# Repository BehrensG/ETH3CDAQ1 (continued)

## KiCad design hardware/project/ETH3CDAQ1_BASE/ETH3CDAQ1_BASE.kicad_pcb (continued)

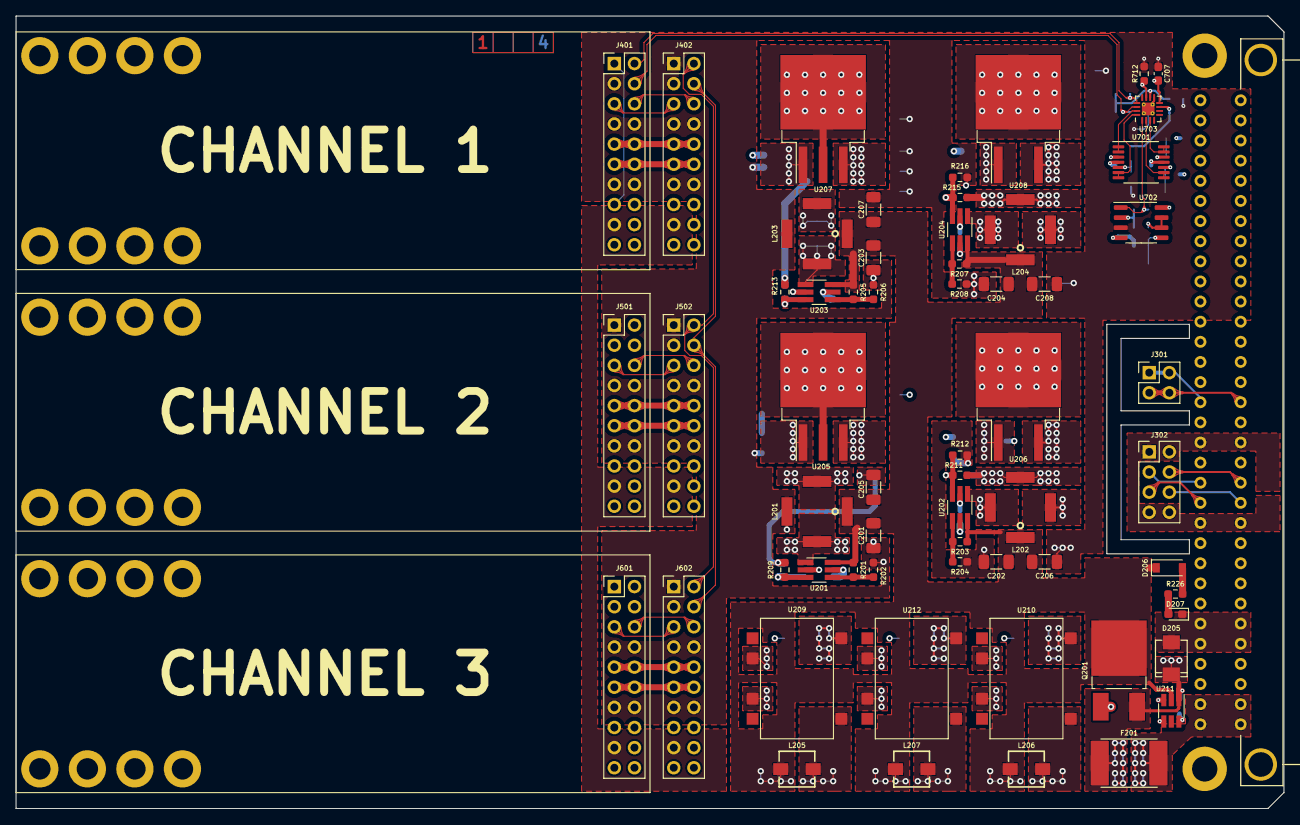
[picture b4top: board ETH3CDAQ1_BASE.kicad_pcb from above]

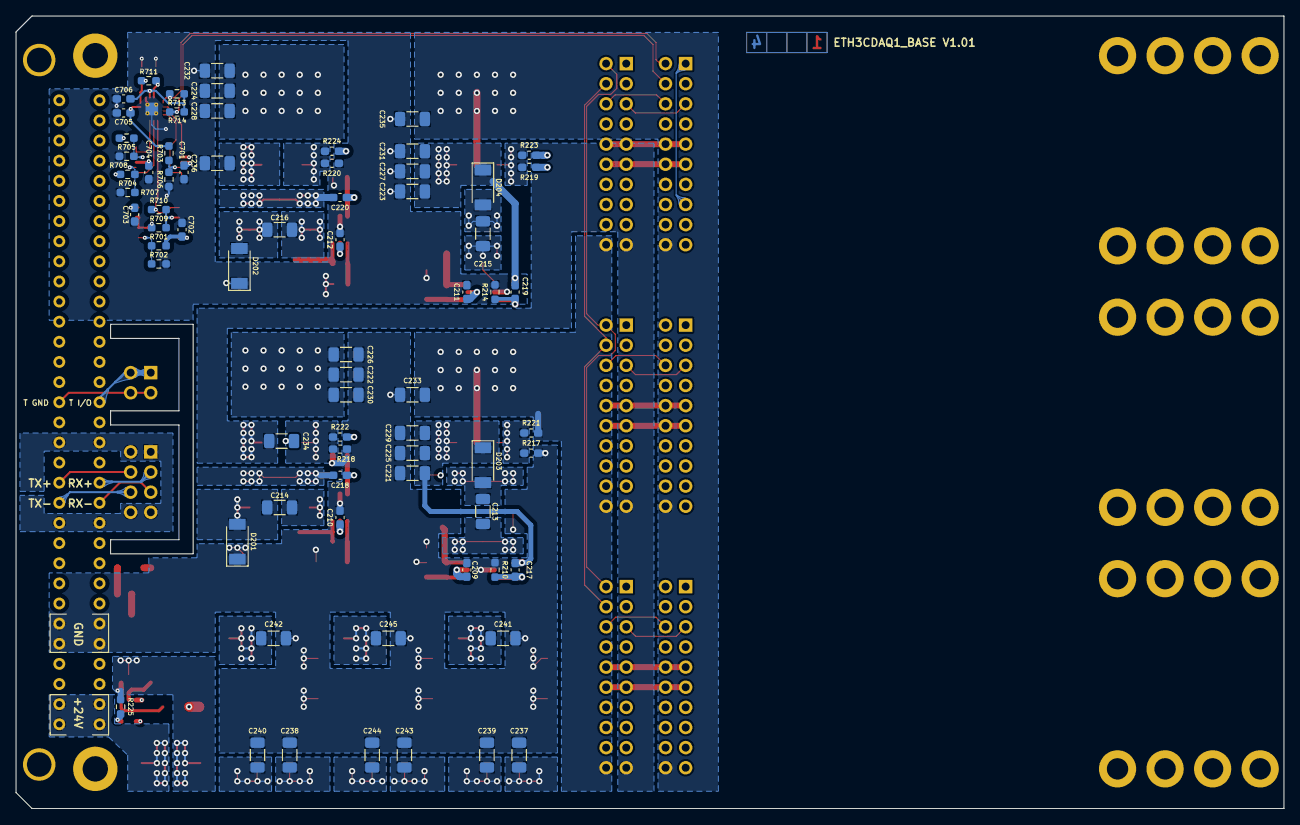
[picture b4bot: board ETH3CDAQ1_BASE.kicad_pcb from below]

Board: 4 copper layers, 160.0 x 100.0 mm, 158 parts (71 on the bottom side), 80 nets.

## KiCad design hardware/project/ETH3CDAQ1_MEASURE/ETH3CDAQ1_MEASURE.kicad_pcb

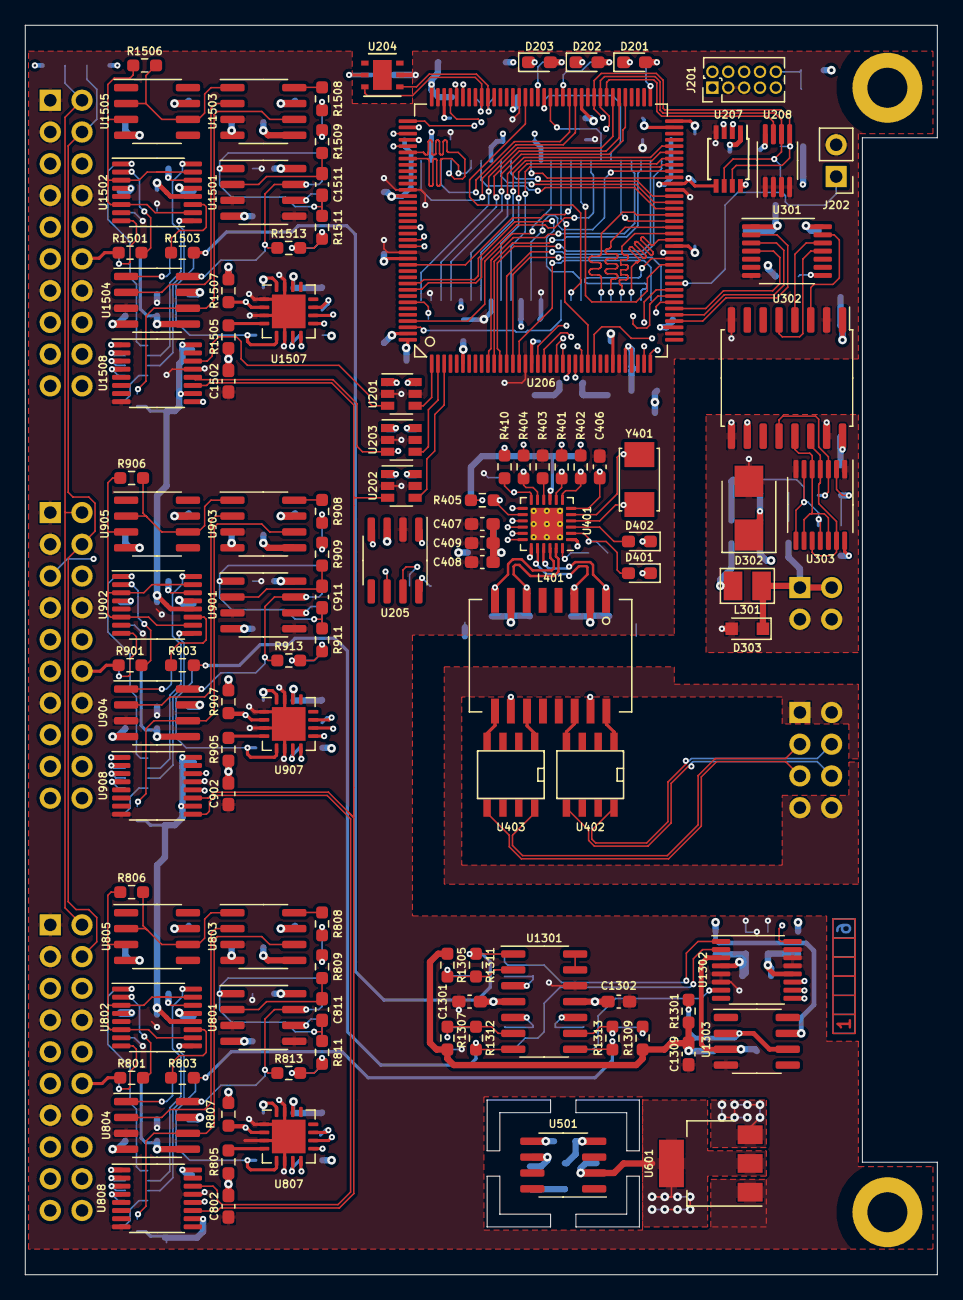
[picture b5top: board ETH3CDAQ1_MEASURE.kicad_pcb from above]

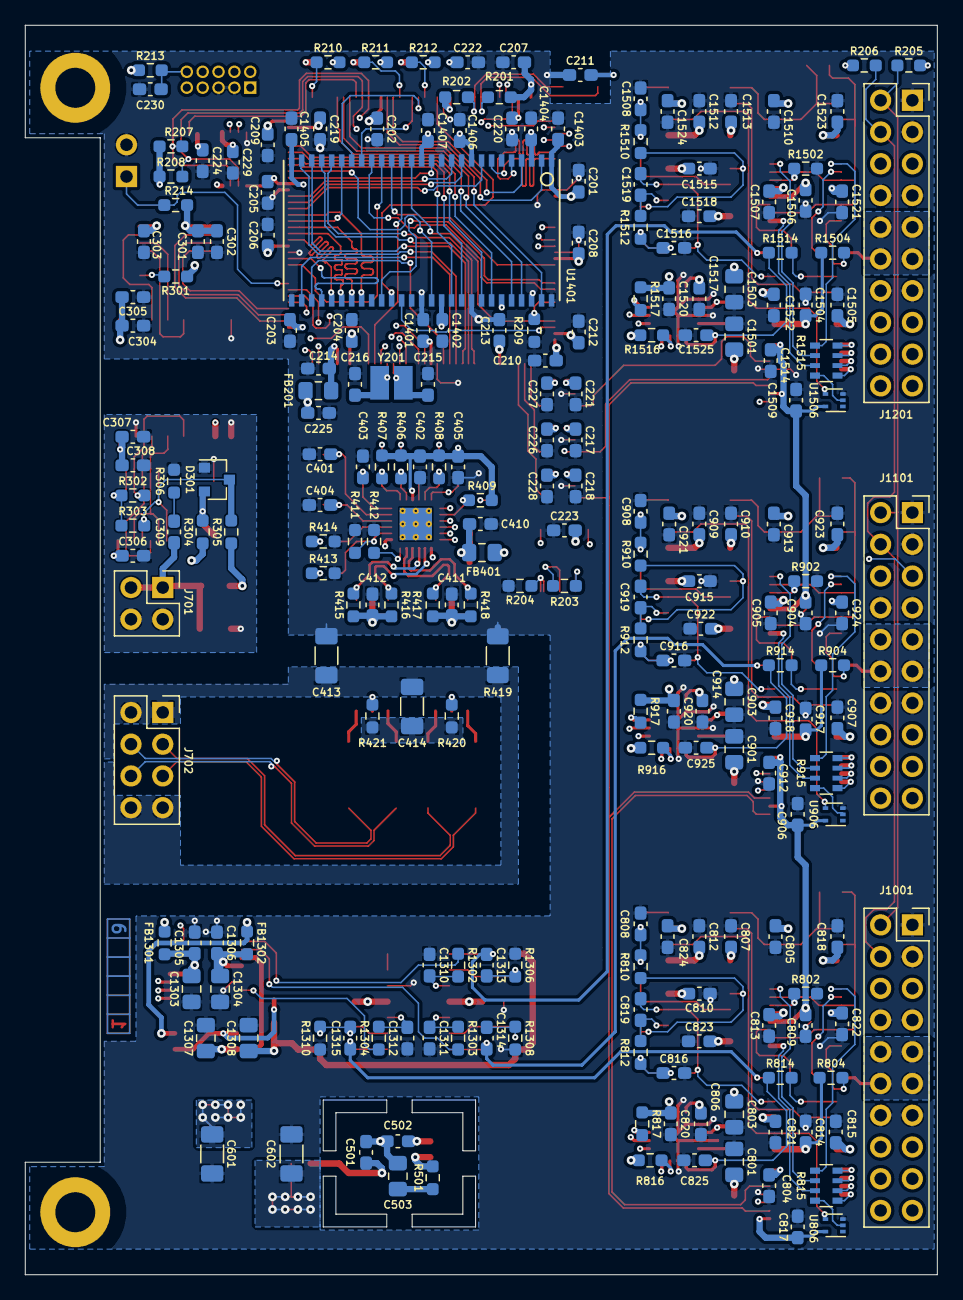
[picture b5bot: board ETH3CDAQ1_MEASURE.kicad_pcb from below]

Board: 6 copper layers, 73.0 x 100.0 mm, 330 parts (223 on the bottom side), 259 nets.

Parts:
C201, C202, C203, C204, C205, C206, C207, C208, C209, C210, C211, C212, C213, C217, C218, C221, C223, C224, C225, C226, C227, C228, C229, C230, C301, C303, C304, C306, C308, C402, C405, C408, C409, C410, C411, C412, C804, C805, C806, C807, C809, C810, C812, C813, C814, C815, C817, C818, C820, C821, C822, C823, C824, C904, C905, C906, C907, C909, C910, C912, C913, C914, C915, C917, C918, C920, C921, C922, C923, C924, C1301, C1302, C1305, C1306, C1309, C1401, C1402, C1403, C1404, C1405, C1406, C1407, C1504, C1505, C1506, C1507, C1509, C1510, C1512, C1513, C1514, C1515, C1517, C1518, C1520, C1521, C1522, C1523, C1524: 100n; C_0603_1608Metric_Pad1.08x0.95mm_HandSolder
C214, C222, C302, C305, C307, C406, C407, C501, C502, C802, C902, C1502: 1u; C_0603_1608Metric_Pad1.08x0.95mm_HandSolder
C215, C216, C401, C404: 8p; C_0603_1608Metric_Pad1.08x0.95mm_HandSolder
C219, C220: 2u2; C_0603_1608Metric_Pad1.08x0.95mm_HandSolder
C309, C819, C919, C1519: 47p; C_0603_1608Metric_Pad1.08x0.95mm_HandSolder
C403: 470p; C_0603_1608Metric_Pad1.08x0.95mm_HandSolder
C413, C414: 1n/1kV; C_1206_3216Metric_Pad1.33x1.80mm_HandSolder
C503, C803, C903, C1303, C1304, C1503: 10u; C_0805_2012Metric_Pad1.18x1.45mm_HandSolder
C601, C602: 10u; C_1206_3216Metric_Pad1.33x1.80mm_HandSolder
C801, C901, C1501: 22u; C_0805_2012Metric_Pad1.18x1.45mm_HandSolder
C808, C825, C908, C925, C1508, C1525: 330p; C_0603_1608Metric_Pad1.08x0.95mm_HandSolder
C811, C911, C1511: 100p; C_0603_1608Metric_Pad1.08x0.95mm_HandSolder
C816, C916, C1516: 1000p; C_0603_1608Metric_Pad1.08x0.95mm_HandSolder
C1307, C1308: 4u7; C_0805_2012Metric_Pad1.18x1.45mm_HandSolder
C1310, C1311, C1312: 220n; C_0603_1608Metric_Pad1.08x0.95mm_HandSolder
C1313, C1314, C1315: 1n; C_0603_1608Metric_Pad1.08x0.95mm_HandSolder
D201: RED; LED_0603_1608Metric_Pad1.05x0.95mm_HandSolder
D202, D402: GREEN; LED_0603_1608Metric_Pad1.05x0.95mm_HandSolder
D203: BLUE; LED_0603_1608Metric_Pad1.05x0.95mm_HandSolder
D301: BAV99; SOT-23
D302: SMBJ5.0A; D_SMB
D303: SD36C-01FTG; D_SOD-323_HandSoldering
D401: YELLOW; LED_0603_1608Metric_Pad1.05x0.95mm_HandSolder
FB201, FB401: 742792031; L_0805_2012Metric_Pad1.15x1.40mm_HandSolder
FB1301, FB1302: MPZ1608S221ATA00; R_0603_1608Metric_Pad0.98x0.95mm_HandSolder
H101, H102: MountingHole; MountingHole_3.2mm_M3_DIN965_Pad
J201: 20021111-00010T4LF; PinHeader_2x05_P1.27mm_Vertical
J202: Conn_02x01; PinHeader_1x02_P2.54mm_Vertical
J701: Conn_02x02_Odd_Even; PinSocket_2x02_P2.54mm_Vertical
J702: Conn_02x04_Odd_Even; PinSocket_2x04_P2.54mm_Vertical
J1001, J1101, J1201: Conn_02x10_Odd_Even; PinSocket_2x10_P2.54mm_Vertical
L301: CW252016-R33G; CW252016
L401: 749010012A
R201, R202, R205, R206, R207, R208: 4k7; R_0603_1608Metric_Pad0.98x0.95mm_HandSolder
R203: 120; R_0603_1608Metric_Pad0.98x0.95mm_HandSolder
R204: R; R_0603_1608Metric_Pad0.98x0.95mm_HandSolder
R209, R213, R214, R301, R403, R406, R407, R408, R409, R411, R802, R803, R816, R817, R902, R903, R916, R917, R1502, R1503, R1516, R1517: 10k; R_0603_1608Metric_Pad0.98x0.95mm_HandSolder
R210, R212: 680; R_0603_1608Metric_Pad0.98x0.95mm_HandSolder
R211: 560; R_0603_1608Metric_Pad0.98x0.95mm_HandSolder
R302: 14k7; R_0603_1608Metric_Pad0.98x0.95mm_HandSolder
R303: 100; R_0603_1608Metric_Pad0.98x0.95mm_HandSolder
R304, R1302, R1303, R1304: 1k; R_0603_1608Metric_Pad0.98x0.95mm_HandSolder
R305: 47; R_0603_1608Metric_Pad0.98x0.95mm_HandSolder
R306: 51R1; R_0603_1608Metric_Pad0.98x0.95mm_HandSolder
R401, R402, R404, R405: 33; R_0603_1608Metric_Pad0.98x0.95mm_HandSolder
R410: 1k5; R_0603_1608Metric_Pad0.98x0.95mm_HandSolder
R412: 12k1; R_0603_1608Metric_Pad0.98x0.95mm_HandSolder
R413, R414: 270; R_0603_1608Metric_Pad0.98x0.95mm_HandSolder
R415, R416, R417, R418, R804, R904, R1504: 49R9; R_0603_1608Metric_Pad0.98x0.95mm_HandSolder
R419: 1M/1kV; R_1206_3216Metric_Pad1.30x1.75mm_HandSolder
R420, R421: 75/1%; R_0603_1608Metric_Pad0.98x0.95mm_HandSolder
R501, R805, R905, R1505: 0R22; R_0603_1608Metric_Pad0.98x0.95mm_HandSolder
R801, R806, R814, R901, R906, R914, R1501, R1506, R1514: 0; R_0603_1608Metric_Pad0.98x0.95mm_HandSolder
R807, R907, R1507: 0R47; R_0603_1608Metric_Pad0.98x0.95mm_HandSolder
R808, R810, R908, R910, R1508, R1510: 6k81; R_0603_1608Metric_Pad0.98x0.95mm_HandSolder
R809, R909, R1509: 11k3; R_0603_1608Metric_Pad0.98x0.95mm_HandSolder
R811, R813, R911, R913, R1511, R1513: 5k23; R_0603_1608Metric_Pad0.98x0.95mm_HandSolder
R812, R912, R1512: 10k2; R_0603_1608Metric_Pad0.98x0.95mm_HandSolder
R815, R915, R1515: 680; R_Array_Convex_4x0603
R1301: 10; R_0603_1608Metric_Pad0.98x0.95mm_HandSolder
R1305, R1307, R1309: 24k9; R_0603_1608Metric_Pad0.98x0.95mm_HandSolder
R1306, R1308, R1310: 33k2; R_0603_1608Metric_Pad0.98x0.95mm_HandSolder
R1311, R1312, R1313: 100k; R_0603_1608Metric_Pad0.98x0.95mm_HandSolder
U201, U202, U203: SN74LVC1T45DBV; SOT-23-6
U204: HDC1080; Texas_PWSON-N6
U205: MCP2551-I-SN; SOIC-8_3.9x4.9mm_P1.27mm
U206: STM32H743ZI; TQFP-144_20x20mm_P0.5mm
U207: PCA9517; TSSOP-8_3x3mm_P0.65mm
U208: 24LC08B-E/MS; MSOP-8_3x3mm_P0.65mm
U301: TXB0104PW; TSSOP-14_4.4x5mm_P0.65mm
U302: ADuM5402; SOIC-16W_7.5x10.3mm_P1.27mm
U303: 74AC125; TSSOP-14_4.4x5mm_P0.65mm
U401: LAN8742A; QFN-24-1EP_4x4mm_P0.5mm_EP2.6x2.6mm_ThermalVias
U402, U403: LC03-3.3; SO8E
U501: REF5040ID; SOIC-8_3.9x4.9mm_P1.27mm
U601: LM1117-5.0; SOT-223-3_TabPin2
U801, U901, U1501: LT1355; SOIC-8_3.9x4.9mm_P1.27mm
U802, U902, U1502: DG211; TSSOP-16_4.4x5mm_P0.65mm
U803, U804, U903, U904, U1503, U1504: DG419LDY; SOIC-8_3.9x4.9mm_P1.27mm
U805, U905, U1505: OPA192; SOIC-8_3.9x4.9mm_P1.27mm
U806, U906, U1506: 74LVC1GU04DRL; SOT-553
U807, U907, U1507: ADS8681RUM; QFN-16-1EP_4x4mm_P0.65mm_EP2.7x2.7mm
U808, U908, U1508: 74HCT595; TSSOP-16_4.4x5mm_P0.65mm
U1301: TL074; SOIC-14_3.9x8.7mm_P1.27mm
U1302: DAC8564; TSSOP-16_4.4x5mm_P0.65mm
U1303: TL071; SOIC-8_3.9x4.9mm_P1.27mm
U1401: IS42S16400J-xC/MT48LC16M16A2P-6A; TSSOP-54
Y201: NX3225GD-8MHZ; NX3225GD
Y401: NX5032GA-25.000M-LN-CD-1; NX5032GA

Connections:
+3V3: C201.1, C202.1, C203.1, C204.1, C205.1, C206.1, C207.1, C208.1, C209.1, C210.1, C211.1, C212.1, C213.1, C222.1, C224.1, C225.1, C226.1, C227.1, C228.1, C229.1, C301.1, C302.1, C402.1, C405.1, C820.1, C920.1, C1401.1, C1402.1, C1403.1, C1404.1, C1405.1, C1406.1, C1407.1, C1520.1, D201.2, D202.2, D203.2, FB201.2, FB401.2, FB1301.2, J201.1, J1001.15, J1001.16, J1101.15, J1101.16, J1201.15, J1201.16, R201.1, R202.1, R205.1, R206.1, R207.1, R208.1, R213.1, R214.2, R301.1, R406.1, R407.1, R408.1, R409.1, R410.1, R816.1, R817.1, R916.1, R917.1, R1516.1, R1517.1, U201.6, U202.6, U203.6, U204.5, U206.6, U206.17, U206.30, U206.39, U206.52, U206.62, U206.72, U206.84, U206.95, U206.108, U206.121, U206.131, U206.143, U206.144, U207.1, U207.5, U207.8, U208.8, U301.1, U401.9, U807.14, U907.14, U1401.1, U1401.3, U1401.9, U1401.14, U1401.27, U1401.43, U1401.49, U1507.14
+5V: C217.1, C218.1, C221.1, C223.1, C303.1, C304.1, C305.1, C804.1, C806.1, C809.1, C812.1, C814.1, C817.1, C904.1, C906.1, C909.1, C912.1, C914.1, C917.1, C1504.1, C1506.1, C1509.1, C1512.1, C1514.1, C1517.1, J1001.18, J1101.18, J1201.18, R804.2, R904.2, R1504.2, U201.1, U202.1, U203.1, U205.3, U301.14, U302.1, U802.12, U803.5, U804.5, U806.5, U807.16, U808.10, U808.16, U902.12, U903.5, U904.5, U906.5, U907.16, U908.10, U908.16, U1502.12, U1503.5, U1504.5, U1506.5, U1507.16, U1508.10, U1508.16
+5VF: C501.1, C602.1, FB1302.2, U501.2, U601.2, U1303.7
+5V_TRIG: C306.1, C307.1, C308.1, R304.1, U302.10, U302.16, U303.14
+9V: C601.1, J1001.17, J1101.17, J1201.17, U601.3
+18V: C805.1, C807.1, C810.1, C813.1, C815.1, C905.1, C907.1, C910.1, C913.1, C915.1, C1301.1, C1505.1, C1507.1, C1510.1, C1513.1, C1515.1, J1001.20, J1101.20, J1201.20, U801.8, U802.13, U803.4, U804.4, U805.7, U901.8, U902.13, U903.4, U904.4, U905.7, U1301.4, U1501.8, U1502.13, U1503.4, U1504.4, U1505.7
-18V: C818.1, C821.1, C822.1, C823.1, C824.1, C918.1, C921.1, C922.1, C923.1, C924.1, C1302.1, C1518.1, C1521.1, C1522.1, C1523.1, C1524.1, J1001.19, J1101.19, J1201.19, U801.4, U802.4, U803.7, U804.7, U805.4, U901.4, U902.4, U903.7, U904.7, U905.4, U1301.11, U1501.4, U1502.4, U1503.7, U1504.7, U1505.4
/CH1 Connector/CANH: J1001.5, J1101.5, J1201.5, R203.1, U205.7
/CH1 Connector/CANL: J1001.6, J1101.6, J1201.6, R203.2, U205.6
/CH1 Connector/CH1_IN: J1201.9, J1201.10, J1201.11, J1201.12, R1501.2
/CH1 Connector/I2C_SCL: J1001.2, J1101.2, J1201.2, R205.2, U207.2
/CH1 Connector/I2C_SDA: J1001.4, J1101.4, J1201.4, R206.2, U207.3
/CH2 Connector/CH2_IN: J1101.9, J1101.10, J1101.11, J1101.12, R901.2
/CH3 Connector/CH3_IN: J1001.9, J1001.10, J1001.11, J1001.12, R801.2
/Channel 1/ADC1_SCLK: U206.111, U807.10, U907.10, U1507.10
/Channel 1/ADC1_SDI: U206.113, U1507.8
/Channel 1/ADC1_SDO: R1517.2, U907.8, U1507.11
/Channel 1/ADC1_~CS: U206.110, U807.9, U907.9, U1507.9
/Channel 1/CH1_LPF: R1515.4, U1506.2
/Channel 1/CH1_M_DAC: R1515.3, U1502.9
/Channel 1/CH1_M_GND: R1515.2, U1502.16
/Channel 1/CH1_M_IN: R1515.1, U1502.1
/Channel 1/DAC_V1: C1313.1, R1311.1, R1503.2, U1301.1
/Channel 1/REFCAP1: R1505.2, U1507.4
/Channel 1/SR1_QH: U908.14, U1508.9
/Channel 2/ADC2_SDO: R917.2, U807.8, U907.11
/Channel 2/CH2_LPF: R915.4, U906.2
/Channel 2/CH2_M_DAC: R915.3, U902.9
/Channel 2/CH2_M_GND: R915.2, U902.16
/Channel 2/CH2_M_IN: R915.1, U902.1
/Channel 2/DAC_V2: C1314.1, R903.2, R1312.1, U1301.7
/Channel 2/REFCAP2: R905.2, U907.4
/Channel 2/SR2_QH: U808.14, U908.9
/Channel 3/ADC3_SDO: R817.2, U206.112, U807.11
/Channel 3/CH3_LPF: R815.4, U806.2
/Channel 3/CH3_M_DAC: R815.3, U802.9
/Channel 3/CH3_M_GND: R815.2, U802.16
/Channel 3/CH3_M_IN: R815.1, U802.1
/Channel 3/DAC_V3: C1315.1, R803.2, R1313.1, U1301.8
/Channel 3/REFCAP3: R805.2, U807.4
/Connector 1/EXT_TRIG: C309.1, D303.1, J701.1, J701.2, L301.1
/Connector 1/RX+: J702.3, U403.8
/Connector 1/RX-: J702.5, U403.5
/Connector 1/TX+: J702.4, U402.8
/Connector 1/TX-: J702.6, U402.5
/DAC/+2V5REF: C1308.1, C1309.1, R1301.1, R1305.2, R1307.2, R1309.2
/DAC/DAC_0-2V5_VOUT1: R1302.2, U1302.1
/DAC/DAC_0-2V5_VOUT2: R1303.2, U1302.2
/DAC/DAC_0-2V5_VOUT3: R1304.2, U1302.7
/DAC/DAC_DIN: U206.21, U1302.11
/DAC/DAC_LDAC: U206.22, U1302.16
/DAC/DAC_SCLK: U206.19, U1302.10
/DAC/DAC_~SYNC: U206.18, U1302.9
/Ethernet/ETH_RXN: L401.8, R418.2, U401.22
/Ethernet/ETH_RXP: L401.6, R417.2, U401.23
/Ethernet/ETH_TXN: L401.3, R416.2, U401.20
/Ethernet/ETH_TXP: L401.1, R415.2, U401.21
/Ethernet/MODE0: R401.1, R406.2, U401.8
/Ethernet/MODE1: R402.1, R407.2, U401.7
/Ethernet/MODE2: R404.1, R408.2, U401.11
/Ethernet/NRST: C230.1, J201.10, R213.2, U206.25, U401.15
/Ethernet/REFCLK0: R405.1, R409.2, U401.14
/Ethernet/REF_CLK: R405.2, U206.35
/Ethernet/RMII_CRS_DV: R404.2, U206.43
/Ethernet/RMII_MDC: U206.27, U401.13
/Ethernet/RMII_MDIO: R410.2, U206.36, U401.12
/Ethernet/RMII_RXD0: R401.2, U206.44
/Ethernet/RMII_RXD1: R402.2, U206.45
/Ethernet/RMII_TXD0: U206.128, U401.17
/Ethernet/RMII_TXD1: U206.129, U401.18
/Ethernet/RMII_TXEN: U206.126, U401.16
/MCU/A0: U206.10, U1401.23
/MCU/A1: U206.11, U1401.24
/MCU/A2: U206.12, U1401.25
/MCU/A3: U206.13, U1401.26
/MCU/A4: U206.14, U1401.29
/MCU/A5: U206.15, U1401.30
/MCU/A6: U206.50, U1401.31
/MCU/A7: U206.53, U1401.32
/MCU/A8: U206.54, U1401.33
/MCU/A9: U206.55, U1401.34
/MCU/A10: U206.56, U1401.22
/MCU/A11: U206.57, U1401.35
/MCU/BA0: U206.89, U1401.20
/MCU/BA1: U206.90, U1401.21
/MCU/CAN_RX: U205.4, U206.103
/MCU/CAN_TX: U205.1, U206.104
/MCU/CKE: U206.135, U1401.37
/MCU/CLK: U206.93, U1401.38
/MCU/D0: U206.85, U1401.2
/MCU/D1: U206.86, U1401.4
/MCU/D2: U206.114, U1401.5
/MCU/D3: U206.115, U1401.7
/MCU/D4: U206.58, U1401.8
/MCU/D5: U206.59, U1401.10
/MCU/D6: U206.60, U1401.11
/MCU/D7: U206.63, U1401.13
/MCU/D8: U206.64, U1401.42
/MCU/D9: U206.65, U1401.44
/MCU/D10: U206.66, U1401.45
/MCU/D11: U206.67, U1401.47
/MCU/D12: U206.68, U1401.48
/MCU/D13: U206.77, U1401.50
/MCU/D14: U206.78, U1401.51
/MCU/D15: U206.79, U1401.53
/MCU/EEPROM_SCL: R208.2, U206.81, U207.6, U208.6
/MCU/EEPROM_SDA: R207.2, U206.82, U207.7, U208.5
/MCU/EEPROM_WP: U206.80, U208.7
/MCU/LDQM: U206.141, U1401.15
/MCU/MCU_SR_CLK: U202.4, U206.3
/MCU/MCU_SR_DAT: U201.4, U206.1
/MCU/MCU_SR_LAT: U203.4, U206.2
/MCU/MCU_VDDA: C214.1, FB201.1, U206.32, U206.33
/MCU/SD_CLK: U202.3, U808.11, U908.11, U1508.11
/MCU/SD_DAT: U201.3, U1508.14
/MCU/SD_LAT: U203.3, U808.12, U908.12, U1508.12
/MCU/SENS_SCL: R201.2, U204.6, U206.100
/MCU/SENS_SDA: R202.2, U204.1, U206.99
/MCU/TCK_SWCLK: J201.4, U206.109
/MCU/TMS_SWDIO: J201.2, U206.105
/MCU/TRIG_EN: U206.40, U301.2
/MCU/TRIG_IN: U206.42, U301.4
/MCU/TRIG_OUT: U206.41, U301.3
/MCU/UDQM: U206.142, U1401.39
/MCU/~CAS: U206.132, U1401.17
/MCU/~CS: U206.136, U1401.19
/MCU/~RAS: U206.49, U1401.18
/MCU/~WE: U206.26, U1401.16
/Trigger/EXT_TRIG_SIGN: R302.1, U302.12, U303.3
/Trigger/TRIG_OUT_EN: U302.14, U303.4, U303.10, U303.13
/Trigger/TRIG_OUT_SIGN: U302.13, U303.5, U303.9, U303.12
Earth: C413.1, C414.2, J702.1, J702.2, J702.7, J702.8, R419.1
GND: C201.2, C202.2, C203.2, C204.2, C205.2, C206.2, C207.2, C208.2, C209.2, C210.2, C211.2, C212.2, C213.2, C214.2, C215.2, C216.2, C217.2, C218.2, C219.2, C220.2, C221.2, C222.2, C223.2, C224.2, C225.2, C226.2, C227.2, C228.2, C229.2, C230.2, C301.2, C302.2, C303.2, C304.2, C305.2, C401.2, C402.2, C403.2, C404.2, C405.2, C406.2, C407.2, C408.2, C409.2, C410.2, C411.2, C412.2, C413.2, C501.2, C502.2, C503.2, C601.2, C602.2, C801.2, C802.2, C803.2, C804.2, C805.2, C806.2, C807.2, C808.2, C809.2, C810.2, C812.2, C813.2, C814.2, C815.2, C816.2, C817.2, C818.2, C820.2, C821.2, C822.2, C823.2, C824.2, C825.2, C901.2, C902.2, C903.2, C904.2, C905.2, C906.2, C907.2, C908.2, C909.2, C910.2, C912.2, C913.2, C914.2, C915.2, C916.2, C917.2, C918.2, C920.2, C921.2, C922.2, C923.2, C924.2, C925.2, C1301.2, C1302.2, C1303.2, C1304.2, C1305.2, C1306.2, C1307.2, C1308.2, C1309.2, C1310.2, C1311.2, C1312.2, C1401.2, C1402.2, C1403.2, C1404.2, C1405.2, C1406.2, C1407.2, C1501.2, C1502.2, C1503.2, C1504.2, C1505.2, C1506.2, C1507.2, C1508.2, C1509.2, C1510.2, C1512.2, C1513.2, C1514.2, C1515.2, C1516.2, C1517.2, C1518.2, C1520.2, C1521.2, C1522.2, C1523.2, C1524.2, C1525.2, J201.3, J201.5, J202.2, J1001.1, J1001.3, J1001.7, J1001.8, J1001.13, J1001.14, J1101.1, J1101.3, J1101.7, J1101.8, J1101.13, J1101.14, J1201.1, J1201.3, J1201.7, J1201.8, J1201.13, J1201.14, R204.2, R209.2, R403.2, R411.2, R412.1, R413.2, R414.2, R419.2, R802.2, R902.2, R1306.2, R1308.2, R1310.2, R1502.2, U201.2, U201.5, U202.2, U202.5, U203.2, U203.5, U204.2, U205.2, U206.16, U206.31, U206.38, U206.51, U206.61, U206.83, U206.94, U206.107, U206.120, U206.130, U207.4, U208.1, U208.2, U208.3, U208.4, U301.7, U302.2, U302.8, U401.25, U501.4, U601.1, U801.3, U801.5, U802.5, U803.3, U804.3, U806.3, U807.1, U807.3, U807.6, U807.15, U807.17, U808.8, U808.13, U901.3, U901.5, U902.5, U903.3, U904.3, U906.3, U907.1, U907.3, U907.6, U907.15, U907.17, U908.8, U908.13, U1301.12, U1302.5, U1302.6, U1302.13, U1302.14, U1302.15, U1303.4, U1401.6, U1401.12, U1401.28, U1401.41, U1401.46, U1401.52, U1401.54, U1501.3, U1501.5, U1502.5, U1503.3, U1504.3, U1506.3, U1507.1, U1507.3, U1507.6, U1507.15, U1507.17, U1508.8, U1508.13
GND_TRIG: C306.2, C307.2, C308.2, D301.1, D302.2, D303.2, J701.3, J701.4, R306.2, U302.9, U302.15, U303.1, U303.7
unnamed: C215.1, U206.23, Y201.1
unnamed: C216.1, U206.24, Y201.2
unnamed: C219.1, U206.71
unnamed: C220.1, U206.106
unnamed: C309.2, R306.1
unnamed: C401.1, U401.5, Y401.2
unnamed: C403.1, C406.1, U401.6
unnamed: C404.1, U401.4, Y401.1
unnamed: C414.1, R420.2, R421.2
unnamed: C502.1, U501.5
unnamed: C503.1, R501.2
unnamed: C801.1, C802.1, R805.1
unnamed: C803.1, R807.2
unnamed: C808.1, R808.1, R809.2, R810.2
unnamed: C811.1, R810.1, R811.2, U801.1
unnamed: C811.2, R809.1, U801.2
unnamed: C816.1, R811.1, R812.2, R813.2
unnamed: C819.1, R813.1, U801.7, U804.8
unnamed: C819.2, R812.1, U801.6
unnamed: C825.1, R814.1, U807.5
unnamed: C901.1, C902.1, R905.1
unnamed: C903.1, R907.2
unnamed: C908.1, R908.1, R909.2, R910.2
unnamed: C911.1, R910.1, R911.2, U901.1
unnamed: C911.2, R909.1, U901.2
unnamed: C916.1, R911.1, R912.2, R913.2
unnamed: C919.1, R913.1, U901.7, U904.8
unnamed: C919.2, R912.1, U901.6
unnamed: C925.1, R914.1, U907.5
unnamed: C1303.1, C1305.1, FB1301.1, U1302.12
unnamed: C1304.1, C1306.1, FB1302.1, U1302.4
unnamed: C1307.1, U1302.3, U1303.3
unnamed: C1310.1, R1302.1, U1301.3
unnamed: C1311.1, R1303.1, U1301.5
unnamed: C1312.1, R1304.1, U1301.10
unnamed: C1313.2, R1305.1, R1306.1, R1311.2, U1301.2
unnamed: C1314.2, R1307.1, R1308.1, R1312.2, U1301.6
unnamed: C1315.2, R1309.1, R1310.1, R1313.2, U1301.9
unnamed: C1501.1, C1502.1, R1505.1
unnamed: C1503.1, R1507.2
unnamed: C1508.1, R1508.1, R1509.2, R1510.2
unnamed: C1511.1, R1510.1, R1511.2, U1501.1
unnamed: C1511.2, R1509.1, U1501.2
unnamed: C1516.1, R1511.1, R1512.2, R1513.2
unnamed: C1519.1, R1513.1, U1501.7, U1504.8
unnamed: C1519.2, R1512.1, U1501.6
unnamed: C1525.1, R1514.1, U1507.5
unnamed: D201.1, R210.2
unnamed: D202.1, R211.2
unnamed: D203.1, R212.2
unnamed: D301.2, D302.1, R304.2
unnamed: D301.3, R303.2, R305.1, U303.6, U303.8, U303.11
unnamed: D401.1, R413.1
unnamed: D401.2, R411.1, U401.2
unnamed: D402.1, R414.1
unnamed: D402.2, U401.3
unnamed: J202.1, R214.1, U206.46
unnamed: L301.2, R305.2
unnamed: L401.9, U403.4
unnamed: L401.10, R420.1
unnamed: L401.11, U403.1
unnamed: L401.14, U402.4
unnamed: L401.15, R421.1
unnamed: L401.16, U402.1
unnamed: R204.1, U205.8
unnamed: R209.1, U206.138
unnamed: R210.1, U206.73
unnamed: R211.1, U206.87
unnamed: R212.1, U206.91
unnamed: R301.2, U301.8
unnamed: R302.2, R303.1, U303.2
unnamed: R403.1, U401.10
unnamed: R412.2, U401.24
unnamed: R801.1, U802.2
unnamed: R802.1, U802.14
unnamed: R803.1, U802.11
unnamed: R804.1, U802.8
unnamed: R806.1, U803.1, U805.2, U805.6
unnamed: R806.2, U802.3, U802.6, U802.10, U802.15, U805.3
unnamed: R808.2, U803.8
unnamed: R814.2, U804.1
unnamed: R815.5, U808.4
unnamed: R815.6, U808.3
unnamed: R815.7, U808.2
unnamed: R815.8, U808.1
unnamed: R816.2, U807.7
unnamed: R901.1, U902.2
unnamed: R902.1, U902.14
unnamed: R903.1, U902.11
unnamed: R904.1, U902.8
unnamed: R906.1, U903.1, U905.2, U905.6
unnamed: R906.2, U902.3, U902.6, U902.10, U902.15, U905.3
unnamed: R908.2, U903.8
unnamed: R914.2, U904.1
unnamed: R915.5, U908.4
unnamed: R915.6, U908.3
unnamed: R915.7, U908.2
unnamed: R915.8, U908.1
unnamed: R916.2, U907.7
unnamed: R1301.2, U1303.2, U1303.6
unnamed: R1501.1, U1502.2
unnamed: R1502.1, U1502.14
unnamed: R1503.1, U1502.11
unnamed: R1504.1, U1502.8
unnamed: R1506.1, U1503.1, U1505.2, U1505.6
unnamed: R1506.2, U1502.3, U1502.6, U1502.10, U1502.15, U1505.3
unnamed: R1508.2, U1503.8
unnamed: R1514.2, U1504.1
unnamed: R1515.5, U1508.4
unnamed: R1515.6, U1508.3
unnamed: R1515.7, U1508.2
unnamed: R1515.8, U1508.1
unnamed: R1516.2, U1507.7
unnamed: U301.11, U302.5
unnamed: U301.12, U302.4
unnamed: U301.13, U302.3
unnamed: U803.2, U804.2
unnamed: U803.6, U804.6, U806.4
unnamed: U903.2, U904.2
unnamed: U903.6, U904.6, U906.4
unnamed: U1301.13, U1301.14
unnamed: U1503.2, U1504.2
unnamed: U1503.6, U1504.6, U1506.4
VCCQ: C407.1, C408.1, C409.1, C410.1, C411.1, C412.1, FB401.1, L401.2, L401.7, R415.1, R416.1, R417.1, R418.1, U401.1, U401.19
VREF: R501.1, R807.1, R907.1, R1507.1, U501.6, U807.2, U907.2, U1507.2

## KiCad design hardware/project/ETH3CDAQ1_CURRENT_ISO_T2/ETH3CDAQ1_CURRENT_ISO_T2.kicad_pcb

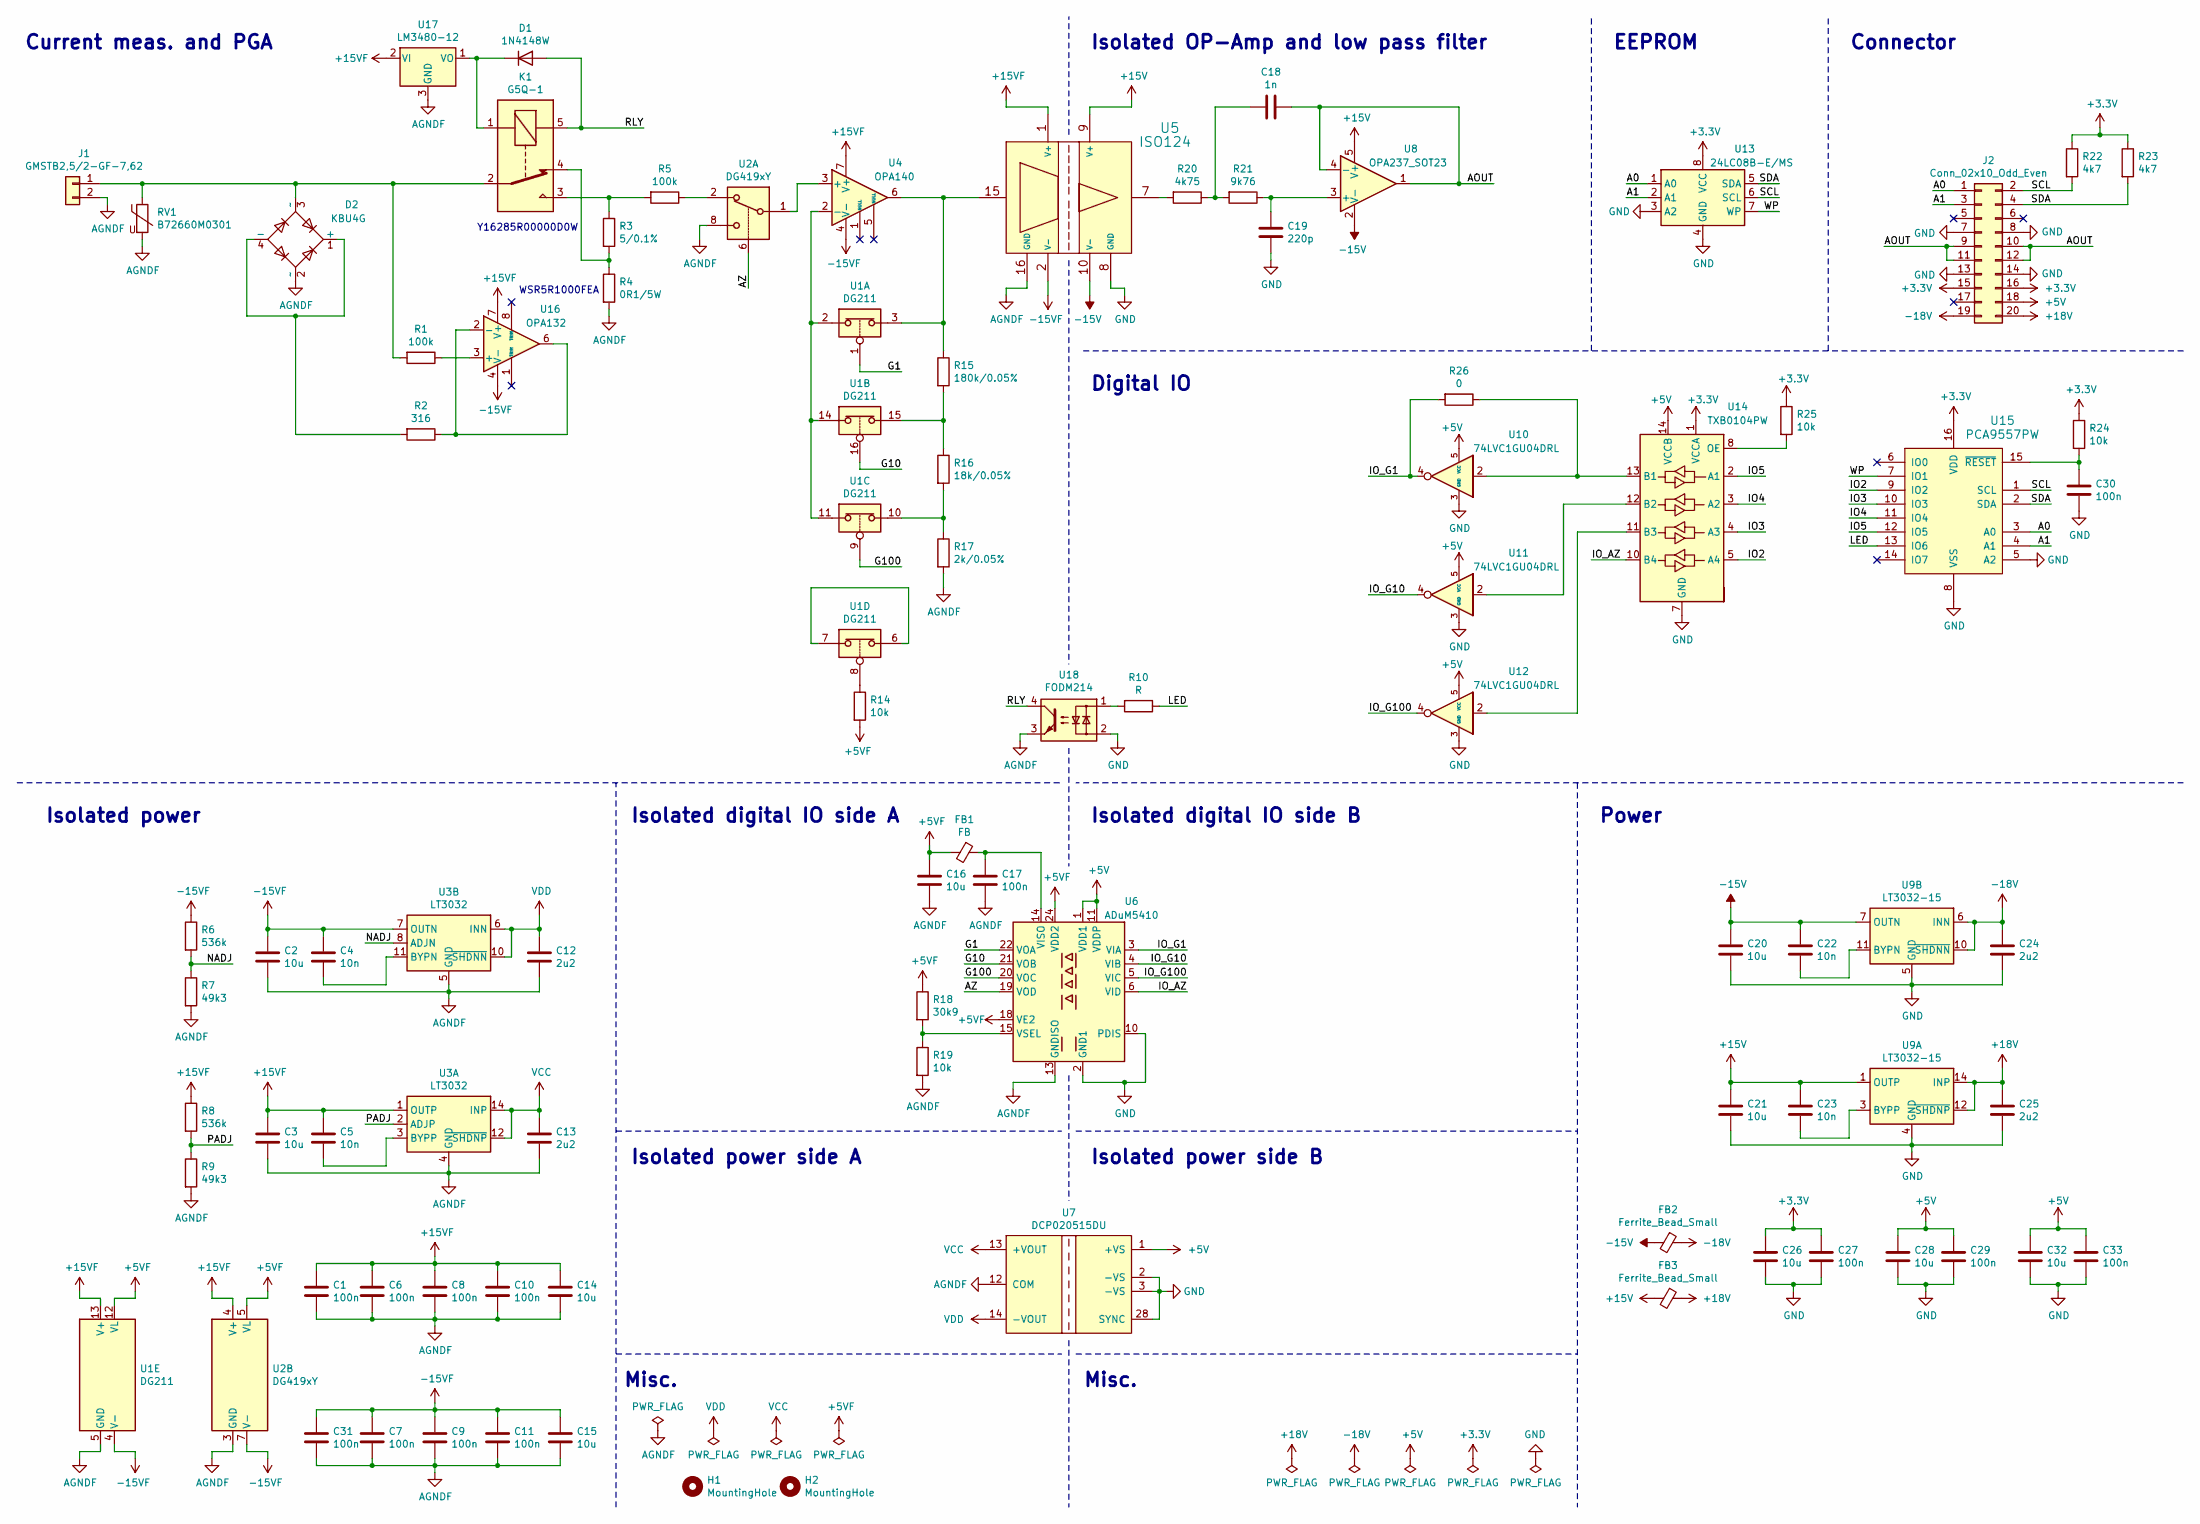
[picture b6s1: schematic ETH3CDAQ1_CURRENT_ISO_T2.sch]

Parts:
C1, C6, C7, C8, C9, C10, C11, C17, C27, C29, C30, C31, C33: 100n; C_0603_1608Metric_Pad1.08x0.95mm_HandSolder
C2, C3, C14, C15, C16, C20, C21, C26, C28, C32: 10u; C_0603_1608Metric_Pad1.08x0.95mm_HandSolder
C4, C5, C22, C23: 10n; C_0603_1608Metric_Pad1.08x0.95mm_HandSolder
C12, C13, C24, C25: 2u2; C_0603_1608Metric_Pad1.08x0.95mm_HandSolder
C18: 1n; C_0603_1608Metric_Pad1.08x0.95mm_HandSolder
C19: 220p; C_0603_1608Metric_Pad1.08x0.95mm_HandSolder
D1: 1N4148W; D_SOD-123
D2: KBU4G; Diode_Bridge_Vishay_KBU
FB1: FB; R_0603_1608Metric_Pad0.98x0.95mm_HandSolder
FB2, FB3: Ferrite_Bead_Small; R_0603_1608Metric_Pad0.98x0.95mm_HandSolder
H1, H2: MountingHole; MountingHole_2.7mm_M2.5_DIN965_Pad
J1: GMSTB2,5/2-GF-7,62; PhoenixContact_GMSTB_2,5_2-GF-7,62_1x02_P7.62mm_Horizontal_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
J2: Conn_02x10_Odd_Even; PinSocket_2x10_P2.54mm_Vertical
K1: G5Q-1; Relay_SPDT_Omron-G5Q-1
R1, R5: 100k; R_0603_1608Metric_Pad0.98x0.95mm_HandSolder
R2: 316; R_0603_1608Metric_Pad0.98x0.95mm_HandSolder
R3: 5/0.1%; R_2512_6332Metric_Pad1.40x3.35mm_HandSolder
R4: 0R1/5W; WSR5
R6, R8: 536k; R_0603_1608Metric_Pad0.98x0.95mm_HandSolder
R7, R9: 49k3; R_0603_1608Metric_Pad0.98x0.95mm_HandSolder
R10: R; R_0603_1608Metric_Pad0.98x0.95mm_HandSolder
R14, R19, R24, R25: 10k; R_0603_1608Metric_Pad0.98x0.95mm_HandSolder
R15: 180k/0.05%; R_0603_1608Metric_Pad0.98x0.95mm_HandSolder
R16: 18k/0.05%; R_0603_1608Metric_Pad0.98x0.95mm_HandSolder
R17: 2k/0.05%; R_0603_1608Metric_Pad0.98x0.95mm_HandSolder
R18: 30k9; R_0603_1608Metric_Pad0.98x0.95mm_HandSolder
R20: 4k75; R_0603_1608Metric_Pad0.98x0.95mm_HandSolder
R21: 9k76; R_0603_1608Metric_Pad0.98x0.95mm_HandSolder
R22, R23: 4k7; R_0603_1608Metric_Pad0.98x0.95mm_HandSolder
R26: 0; R_0603_1608Metric_Pad0.98x0.95mm_HandSolder
RV1: B72660M0301; 4032
U1: DG211; TSSOP-16_4.4x5mm_P0.65mm
U2: DG419xY; SOIC-8_3.9x4.9mm_P1.27mm
U3: LT3032; Linear_DE14MA
U4: OPA140; SOIC-8_3.9x4.9mm_P1.27mm
U5: ISO124; DVA
U6: ADuM5410; SSOP-24_5.3x8.2mm_P0.65mm
U7: DCP020515DU; DVB
U8: OPA237_SOT23; SOT-23-5_HandSoldering
U9: LT3032-15; Linear_DE14MA
U10, U11, U12: 74LVC1GU04DRL; SOT-553
U13: 24LC08B-E/MS; MSOP-8_3x3mm_P0.65mm
U14: TXB0104PW; TSSOP-14_4.4x5mm_P0.65mm
U15: PCA9557PW; TSSOP-16_4.4x5mm_P0.65mm
U16: OPA132; SOIC-8_3.9x4.9mm_P1.27mm
U17: LM3480-12; SOT-23
U18: FODM214; SOP-4_4.4x2.6mm_P1.27mm

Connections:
+3V3: C26.1, C27.1, J2.15, J2.16, R22.1, R23.1, R24.1, R25.1, U13.8 (VCC), U14.1 (VCCA), U15.16 (VDD)
+5V: C28.1, C29.1, C32.1, C33.1, J2.18, U6.1 (VDD1), U6.11 (VDDP), U7.1 (+VS), U10.5 (VCC), U11.5 (VCC), U12.5 (VCC), U14.14 (VCCB)
+5VF: C16.1, FB1.2, R14.2, R18.1, U1.12 (VL), U2.5 (VL), U6.18 (VE2), U6.24 (VDD2)
+15V: C21.1, C23.1, FB3.2, U5.9 (V+), U8.5 (V+), U9.1 (OUTP)
+15VF: C1.1, C3.1, C5.1, C6.1, C8.1, C10.1, C14.1, R8.1, U1.13 (V+), U2.4 (V+), U3.1 (OUTP), U4.7 (V+), U5.1 (V+), U16.7 (V+), U17.2 (VI)
+18V: C25.1, FB3.1, J2.20, U9.12 (~SHDNP), U9.14 (INP)
-15V: C20.1, C22.1, FB2.2, U5.10 (V-), U8.2 (V-), U9.7 (OUTN)
-15VF: C2.1, C4.1, C7.1, C9.1, C11.1, C15.1, C31.1, R6.1, U1.4 (V-), U2.7 (V-), U3.7 (OUTN), U4.4 (V-), U5.2 (V-), U16.4 (V-)
-18V: C24.1, FB2.1, J2.19, U9.6 (INN), U9.9 (INN), U9.10 (~SHDNN)
/A0: J2.1, U13.1 (A0), U15.3 (A0)
/A1: J2.3, U13.2 (A1), U15.4 (A1)
/AOUT: C18.1, J2.9, J2.10, J2.11, J2.12, U8.1, U8.4 (-)
/AZ: U2.6, U6.19 (VOD)
/G1: U1.1, U6.22 (VOA)
/G10: U1.16, U6.21 (VOB)
/G100: U1.9, U6.20 (VOC)
/IO2: U14.5 (A4), U15.9 (IO2)
/IO3: U14.4 (A3), U15.10 (IO3)
/IO4: U14.3 (A2), U15.11 (IO4)
/IO5: U14.2 (A1), U15.12 (IO5)
/IO_AZ: U6.6 (VID), U14.10 (B4)
/IO_G1: R26.2, U6.3 (VIA), U10.4
/IO_G10: U6.4 (VIB), U11.4
/IO_G100: U6.5 (VIC), U12.4
/LED: R10.1, U15.13 (IO6)
/NADJ: R6.2, R7.1, U3.8 (ADJN)
/PADJ: R8.2, R9.1, U3.2 (ADJP)
/RLY: D1.2 (A), K1.5, U18.4
/SCL: J2.2, R22.2, U13.6 (SCL), U15.1 (SCL)
/SDA: J2.4, R23.2, U13.5 (SDA), U15.2 (SDA)
/WP: U13.7 (WP), U15.7 (IO1)
AGNDF: C1.2, C2.2, C3.2, C6.2, C7.2, C8.2, C9.2, C10.2, C11.2, C12.2, C13.2, C14.2, C15.2, C16.2, C17.2, C31.2, D2.2 (~~), J1.2, R4.2, R7.2, R9.2, R17.2, R19.2, RV1.2, U1.5 (GND), U2.3 (GND), U2.8, U3.4 (GND), U3.5 (GND), U5.16 (GND), U6.13 (GNDISO), U6.16 (GNDISO), U6.23 (GNDISO), U7.12 (COM), U17.3 (GND), U18.3
GND: C19.2, C20.2, C21.2, C24.2, C25.2, C26.2, C27.2, C28.2, C29.2, C30.2, C32.2, C33.2, J2.7, J2.8, J2.13, J2.14, U5.8 (GND), U6.2 (GND1), U6.9 (GND1), U6.10 (PDIS), U6.12 (GND1), U7.2 (-VS), U7.3 (-VS), U7.28 (SYNC), U9.4 (GND), U9.5 (GND), U10.3 (GND), U11.3 (GND), U12.3 (GND), U13.3 (A2), U13.4 (GND), U14.7 (GND), U15.5 (A2), U15.8 (VSS), U18.2
unnamed: C4.2, U3.11 (BYPN)
unnamed: C5.2, U3.3 (BYPP)
unnamed: C17.1, FB1.1, U6.14 (VISO)
unnamed: C18.2, R20.1, R21.2
unnamed: C19.1, R21.1, U8.3 (+)
unnamed: C22.2, U9.11 (BYPN)
unnamed: C23.2, U9.3 (BYPP)
unnamed: C30.1, R24.2, U15.15 (~RESET)
unnamed: D1.1 (K), K1.1, U17.1 (VO)
unnamed: D2.1 (+), D2.4 (-), R2.2
unnamed: D2.3 (~~), J1.1, K1.2, R1.2, RV1.1
unnamed: K1.3, R3.1, R5.2
unnamed: K1.4, R3.2, R4.1
unnamed: R1.1, U16.3 (+)
unnamed: R2.1, U16.2 (-), U16.6
unnamed: R5.1, U2.2
unnamed: R10.2, U18.1
unnamed: R14.1, U1.8
unnamed: R15.1, U1.3, U4.6, U5.15
unnamed: R15.2, R16.1, U1.15
unnamed: R16.2, R17.1, U1.10
unnamed: R18.2, R19.1, U6.15 (VSEL)
unnamed: R20.2, U5.7
unnamed: R25.2, U14.8 (OE)
unnamed: R26.1, U10.2, U14.13 (B1)
unnamed: U1.6, U1.7
unnamed: U1.2, U1.11, U1.14, U4.2 (-)
unnamed: U2.1, U4.3 (+)
unnamed: U11.2, U14.12 (B2)
unnamed: U12.2, U14.11 (B3)
VCC: C13.1, U3.12 (~SHDNP), U3.14 (INP), U7.13 (+VOUT)
VDD: C12.1, U3.6 (INN), U3.9 (INN), U3.10 (~SHDNN), U7.14 (-VOUT)

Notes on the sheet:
Current meas. and PGA
Isolated power
Misc.
Digital IO
EEPROM
Connector
Power
Isolated OP-Amp and low pass filter
Isolated digital IO side B
Isolated digital IO side A
Isolated power side A
Isolated power side B
WSR5R1000FEA
Y16285R00000D0W
